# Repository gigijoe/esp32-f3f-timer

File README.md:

# ESP32 F3F Timer by Steve Chang
This is a open source F3F timer base on ESP32 MCU. It supports wire / wifi / CRSF Base A/B trigger input.
Voice report & external buzzer supoort for minimize delay of audio report.

### Hardware
- ESP32 MCU
- Micro SD slot
- PCM5102A audio
- Base A/B wire input
- Wifi antenna
- 2004A Mono LCD display
- Internal buzzer / external buzzer
- DC jack 12V
- 4 buttons

### Software
- F3F timer function (Start / Stop / finish / time report)
- Voice report
- Buzzer sound when Base A/B trigger
- Wifi station
- Support wifi multicast trigger from Base A/B
- Support wire Base A/B trigger
- Support CRSF Base A/B trigger
- LCD display Wifi status / timer / volume adjusted / Base A/B trigger

### Buttons
- [ Stop ] / [ B- ] / [ A+ ] / [ Start ] Buttons

## Idle State
- Wifi Status Page
- Last Record Page
- F3F Mode Page - F3F Training / F3F Competition mode switch by [ A+ ] Button
- Wind Data Page
- Volume Page - Adjust volume by [ A+ ] / [ B- ] Buttons

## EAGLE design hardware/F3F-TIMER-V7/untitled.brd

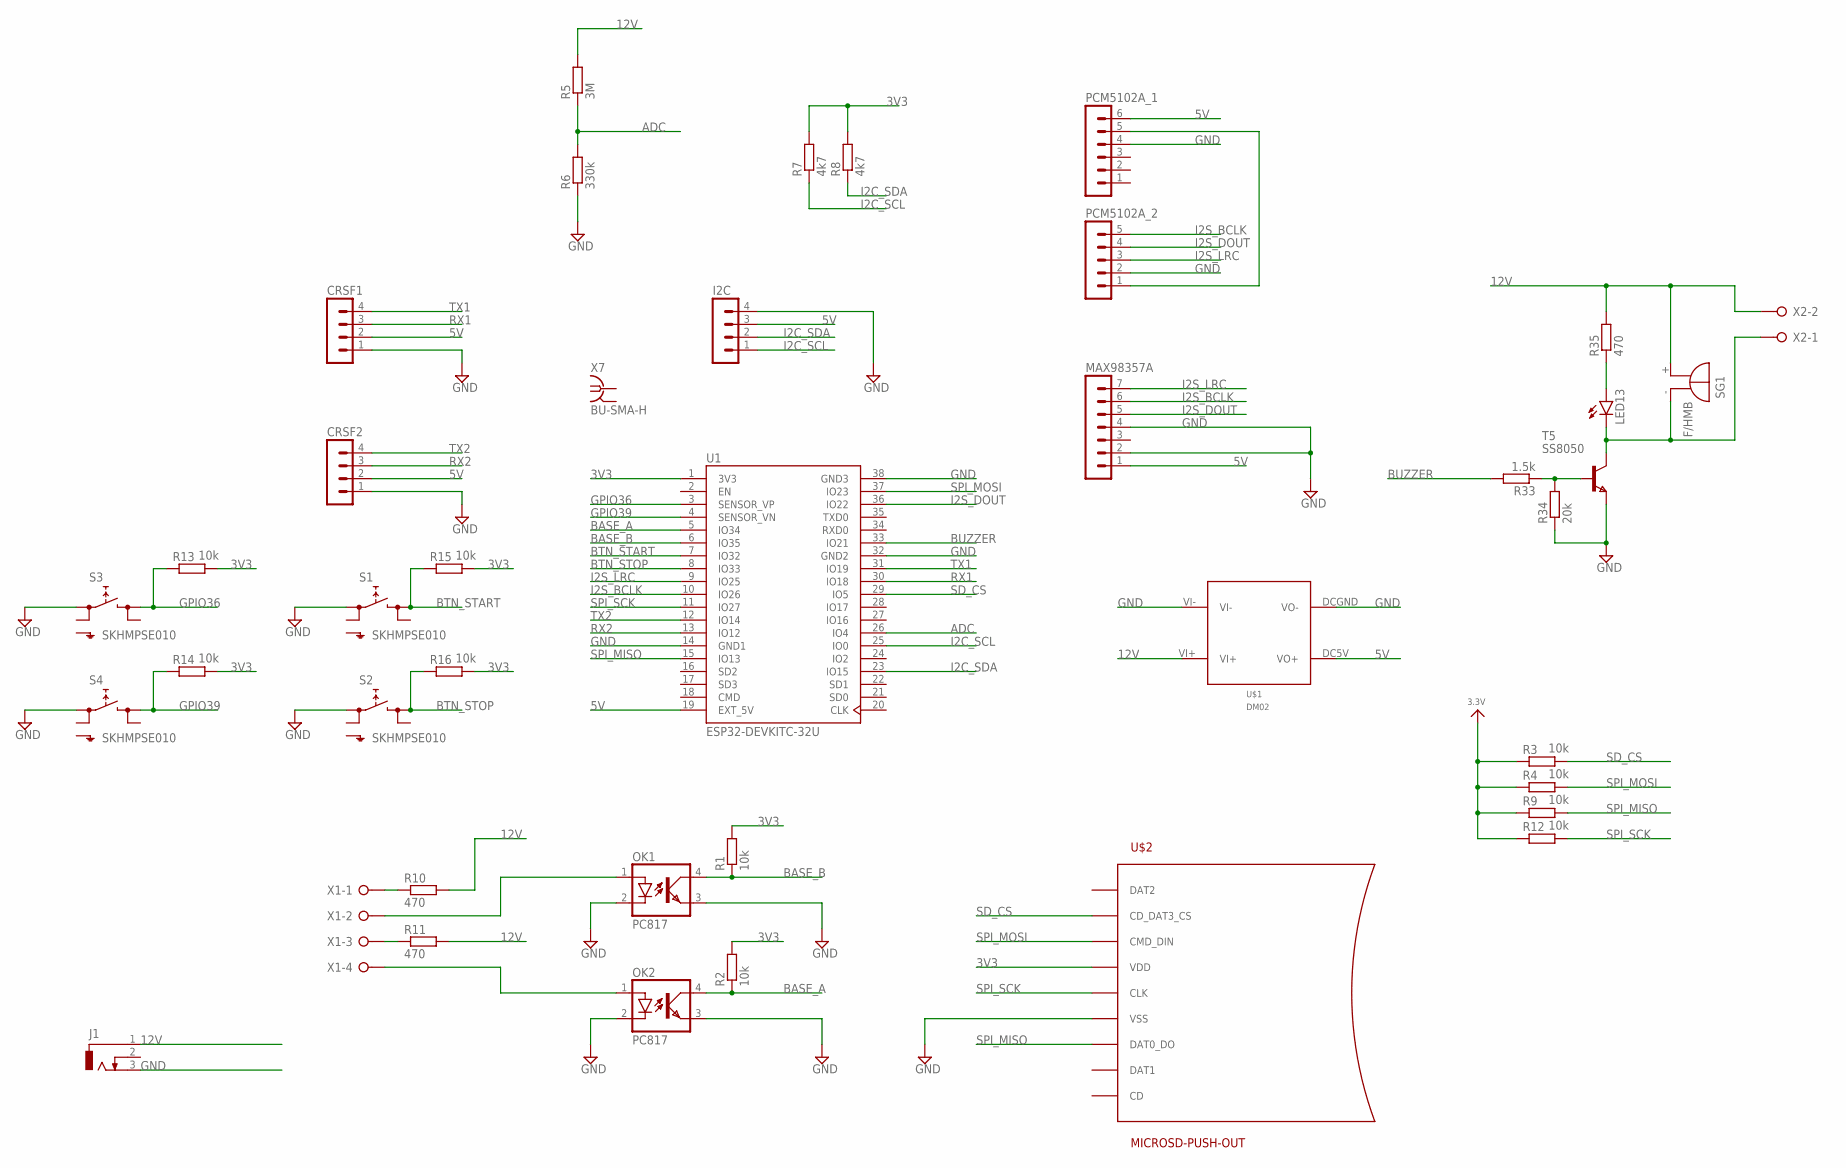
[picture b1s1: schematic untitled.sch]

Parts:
CRSF1, CRSF2: MA04-1
I2C: MA04-1
J1: DCJ0303
LED13: LEDCHIPLED_0805; CHIPLED_0805
MAX98357A: MA07-1
OK1, OK2: PC817; DIL04
PCM5102A_1: MA06-1
PCM5102A_2: MA05-1
R1, R2, R3, R4, R9, R12, R13, R14, R15, R16: 10k; R0603
R5: 3M; R0603
R6: 330k; R0603
R7, R8: 4k7; R0603
R10, R11, R35: 470; R0603
R33: 1.5k; R0603
R34: 20k; R0603
S1, S2, S3, S4: SKHMPSE010; SKHMPXE010
SG1: F/HMB
T5: SS8050; SOT-23
U1: ESP32-DEVKITC-32U; MODULE_ESP32-DEVKITC-32U
U$1: DM02
U$2: MICROSD-PUSH-OUT
X1: W237-04P; W237-4P
X2: W237-02P; W237-132
X7: BU-SMA-H

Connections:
3.3V: R3.1, R4.1, R9.1, R12.1
3V3: R1.2, R2.2, R7.2, R8.2, R13.2, R14.2, R15.2, R16.2, U1.1 (3V3), U$2.4 (VDD)
5V: CRSF1.2, CRSF2.2, I2C.3, MAX98357A.1, PCM5102A_1.6, U1.19 (EXT_5V), U$1.DC5V (VO+)
12V: J1.1, R5.2, R10.2, R11.2, R35.2, SG1.+, U$1.VI+, X2.2
ADC: R5.1, R6.2, U1.26 (IO4)
BASE_A: OK2.4 (COL), R2.1, U1.5 (IO34)
BASE_B: OK1.4 (COL), R1.1, U1.6 (IO35)
BTN_START: R15.1, S1.3 (2.1), U1.7 (IO32)
BTN_STOP: R16.1, S2.3 (2.1), U1.8 (IO33)
BUZZER: R33.2, U1.33 (IO21)
GND: CRSF1.1, CRSF2.1, I2C.4, J1.3, MAX98357A.2, MAX98357A.4, OK1.2 (C), OK1.3 (EMIT), OK2.2 (C), OK2.3 (EMIT), PCM5102A_1.4, PCM5102A_2.2, R6.1, R34.1, S1.1 (1.1), S2.1 (1.1), S3.1 (1.1), S4.1 (1.1), T5.2 (E), U1.14 (GND1), U1.32 (GND2), U1.38 (GND3), U$1.DCGND (VO-), U$1.VI-, U$2.6 (VSS), U$2.G1 (VSS), U$2.G2 (VSS), U$2.G3 (VSS), U$2.G4 (VSS)
GPIO36: R13.1, S3.3 (2.1), U1.3 (SENSOR_VP)
GPIO39: R14.1, S4.3 (2.1), U1.4 (SENSOR_VN)
I2C_SCL: I2C.1, R7.1, U1.25 (IO0)
I2C_SDA: I2C.2, R8.1, U1.23 (IO15)
I2S_BCLK: MAX98357A.6, PCM5102A_2.5, U1.10 (IO26)
I2S_DOUT: MAX98357A.5, PCM5102A_2.4, U1.36 (IO22)
I2S_LRC: MAX98357A.7, PCM5102A_2.3, U1.9 (IO25)
unnamed: OK1.1 (A), X1.2
unnamed: OK2.1 (A), X1.4
unnamed: PCM5102A_1.5, PCM5102A_2.1
unnamed: R10.1, X1.1
unnamed: R11.1, X1.3
unnamed: R33.1, R34.2, T5.3 (B)
unnamed: LED13.A, R35.1
unnamed: LED13.C, SG1.-, T5.1 (C), X2.1
RX1: CRSF1.3, U1.30 (IO18)
RX2: CRSF2.3, U1.13 (IO12)
SD_CS: R3.2, U1.29 (IO5), U$2.2 (CD_DAT3_CS)
SPI_MISO: R9.2, U1.15 (IO13), U$2.7 (DAT0_DO)
SPI_MOSI: R4.2, U1.37 (IO23), U$2.3 (CMD_DIN)
SPI_SCK: R12.2, U1.11 (IO27), U$2.5 (CLK)
TX1: CRSF1.4, U1.31 (IO19)
TX2: CRSF2.4, U1.12 (IO14)

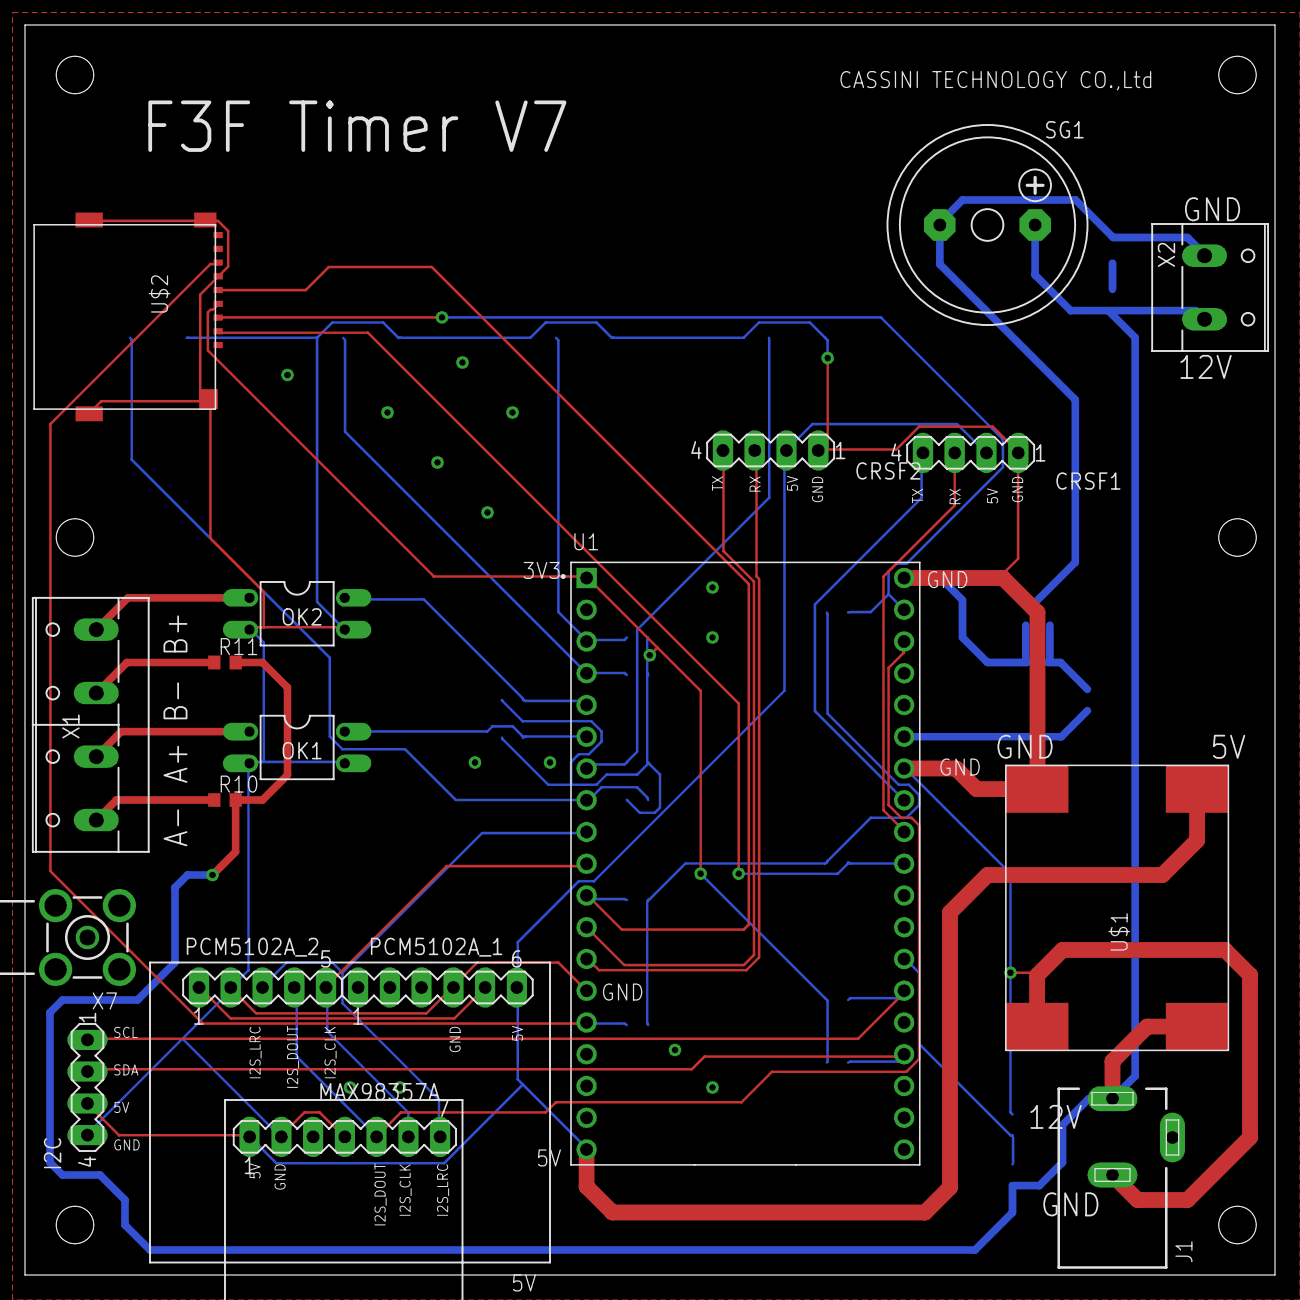
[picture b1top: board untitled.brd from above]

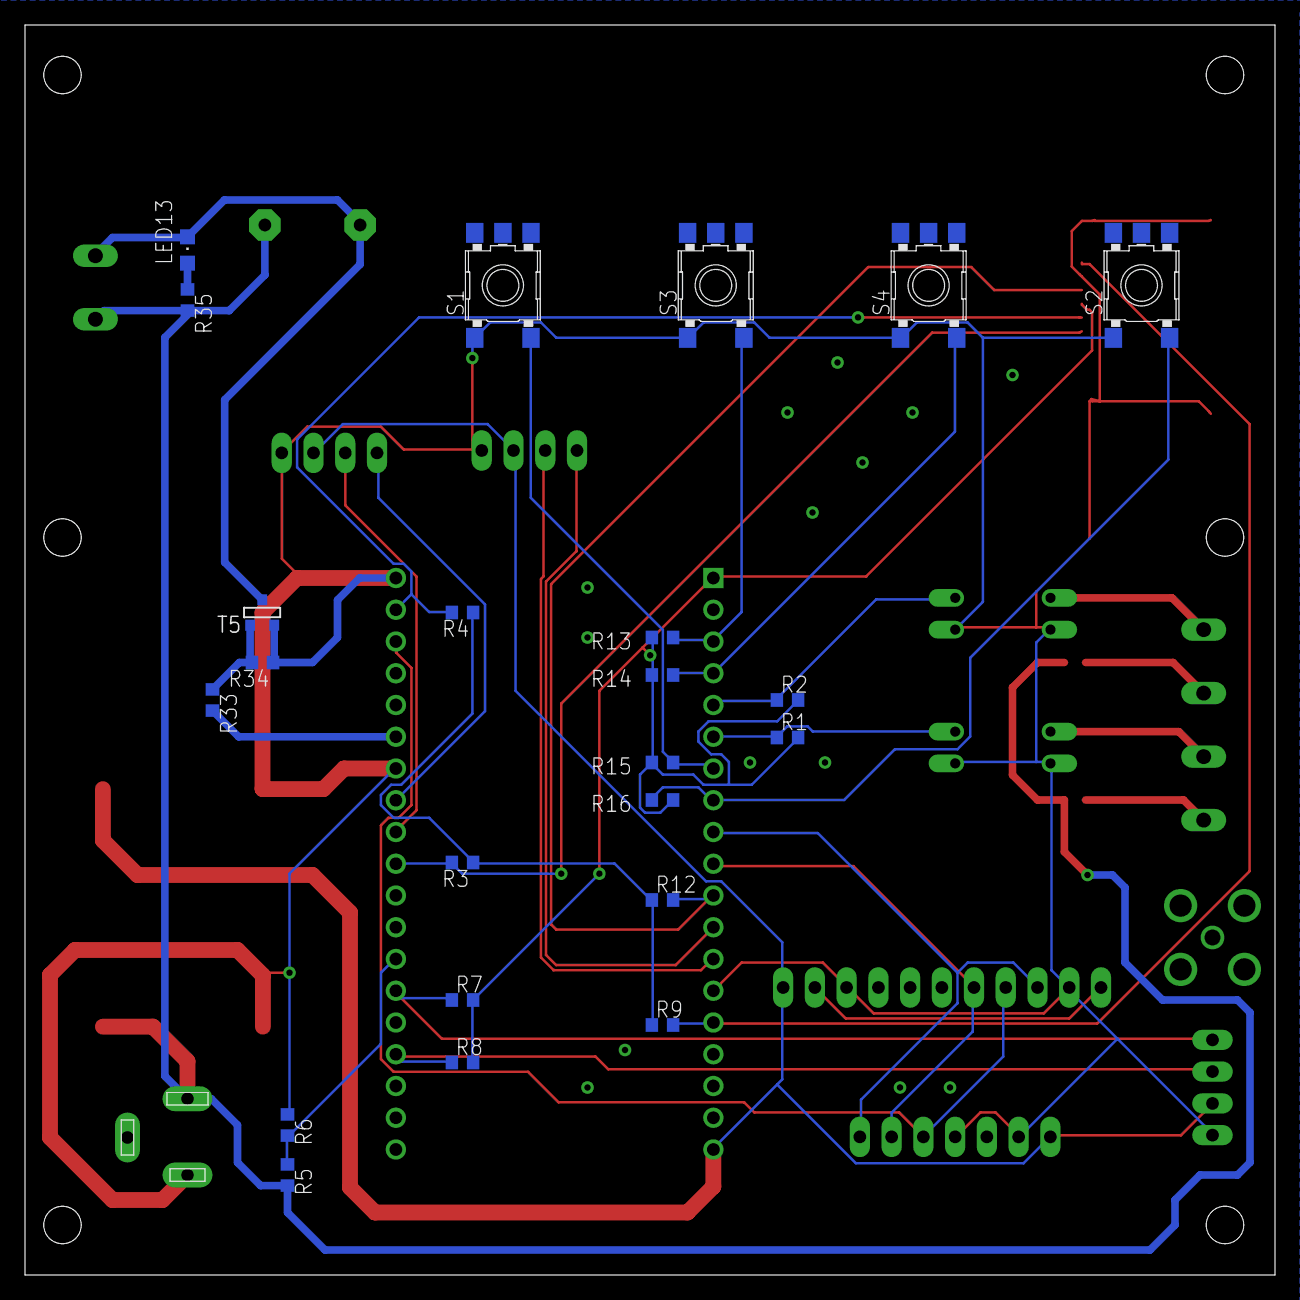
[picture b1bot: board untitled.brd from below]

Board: 2 copper layers, 100.0 x 100.0 mm, 41 parts (23 on the bottom side), 34 nets.

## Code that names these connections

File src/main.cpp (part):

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#include "lcd204.h"
#include "f3f.h"

#define BUZZER 21

void buzzerSetup() {
  pinMode(BUZZER, OUTPUT);
  digitalWrite(BUZZER, LOW);
}

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uint32_t serNoB = 0;

// microSD Card Reader connections
#define SD_CS          5
#define SPI_MOSI      23 
#define SPI_MISO      13
#define SPI_SCK       27

/*
* CRSF
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}
*/

#define BTN_START 32
#define BTN_A 36
#define BTN_B 39
#define BTN_STOP 33

#define BASE_A 34
#define BASE_B 35

void setup() {
  // Set microSD Card CS as OUTPUT and set HIGH
  pinMode(SD_CS, OUTPUT);      
  digitalWrite(SD_CS, HIGH); 

  pinMode(BTN_START, INPUT_PULLUP);      //input pull-up resistor is enabled
  pinMode(BTN_A, INPUT);
  pinMode(BTN_B, INPUT);
  pinMode(BTN_STOP, INPUT_PULLUP);      //input pull-up resistor is enabled

  pinMode(BASE_A, INPUT);      //input pull-up resistor is enabled
  pinMode(BASE_B, INPUT);

/* 
  timer1 = timerBegin(1000);               // 1k Hz
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
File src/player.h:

#ifndef PLAYER_H
#define PLAYER_H

#include <stdint.h>

// I2S Connections
#define I2S_DOUT      22
#define I2S_BCLK      26
#define I2S_LRC       25

void Mp3Player_Init(void);
void Mp3Player_Loop(void);

void Mp3Player_Play(const char *filePath);
void Mp3Player_PlayPriority(const char *filePath);
void Mp3Player_Stop(void);
void Mp3Player_Reset(void);
bool Mp3Player_IsPlaying(void);
const char *Mp3Player_CurrentPlayFile();

uint8_t Mp3Player_GetVolume();
void Mp3Player_SetVolume(uint8_t volume);

#endif

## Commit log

2025-06-20 1.Fix Base trigger UI display bug 2.Set audio volume level to 21 3.Add README.md
2025-06-20 Add hardware
2025-06-23 Support F3F Competition & Training mode
2025-06-24 Add timer jpg
2025-11-06 Improve buzzer timing

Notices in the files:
parts and their libraries:
microbuilder: This work is placed in the public domain, and may be freely used for commercial and non-commercial work with the following conditions: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
